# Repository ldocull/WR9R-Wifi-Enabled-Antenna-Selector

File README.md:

# WR9R-Wifi-Enabled-Antenna-Selector
This PCBA provides a method to remotely control antenna selection within a LAN using a standard browser.  I like to operate my HAM station, which is located in the basement, from other areas in or around my home.  This PCB and Firmware upgrade was easy to apply to my existing [Ameritron RCS-8V](https://mfjenterprises.com/products/rcs-8v) Antenna Selector control box while still maintaining manual control when I am in the basement radio-shack. 

## Key features:

- Directly fits within the existing enclosure
- Supports original manual control but adds remote control 
  (Changing the antenna choice at the front panel at any time, resets the device to the manual selection mode)
- Browser buttons can be named through the browser to support antenna upgrades

## Assembly Installation:

 The control wires were clipped from the back terminal strip and landed to the rear of the PCBA as shown above.
- New wires were the placed from the "To Relays" header to the terminal strip
- 12VDC power was picked up at the DC jack on the rear of the enclosure -- but could be picked up after the from panel switch on the front PCBA.

## Setup:

 The software can be modified and hard coded to your network. Otherwise you can set it up using a phone or other internet-ready device. Connect to the Wifi hotspot generated by the Antenna Selector interface that looks like:  *WR9RasNNN*,  where *NNN* is a somewhat random number.
- Password is '*12345678*'
- On the same device, use a browser to then go to the host address:  https://192.168.4.1/SSID

- There, enter the SSID and Password for the network you wish to use within your LAN
- If you're plugged into the wifi module of the new PCBA with a USB cable, you can use a terminal session to see the new IP.  Otherwise. you will need to log into your router to find the new address assigned to the device.

## Antenna Names:
The buttons on the main screen can be renamed at any time. Just go to **htpps://*yourIPadd*/NAMES**

73
-[WR9R](http://wr9r.com/) 

___
Let us know that this work has been helpful to you.  Any proceeds will be used to offset expenses and further the art.

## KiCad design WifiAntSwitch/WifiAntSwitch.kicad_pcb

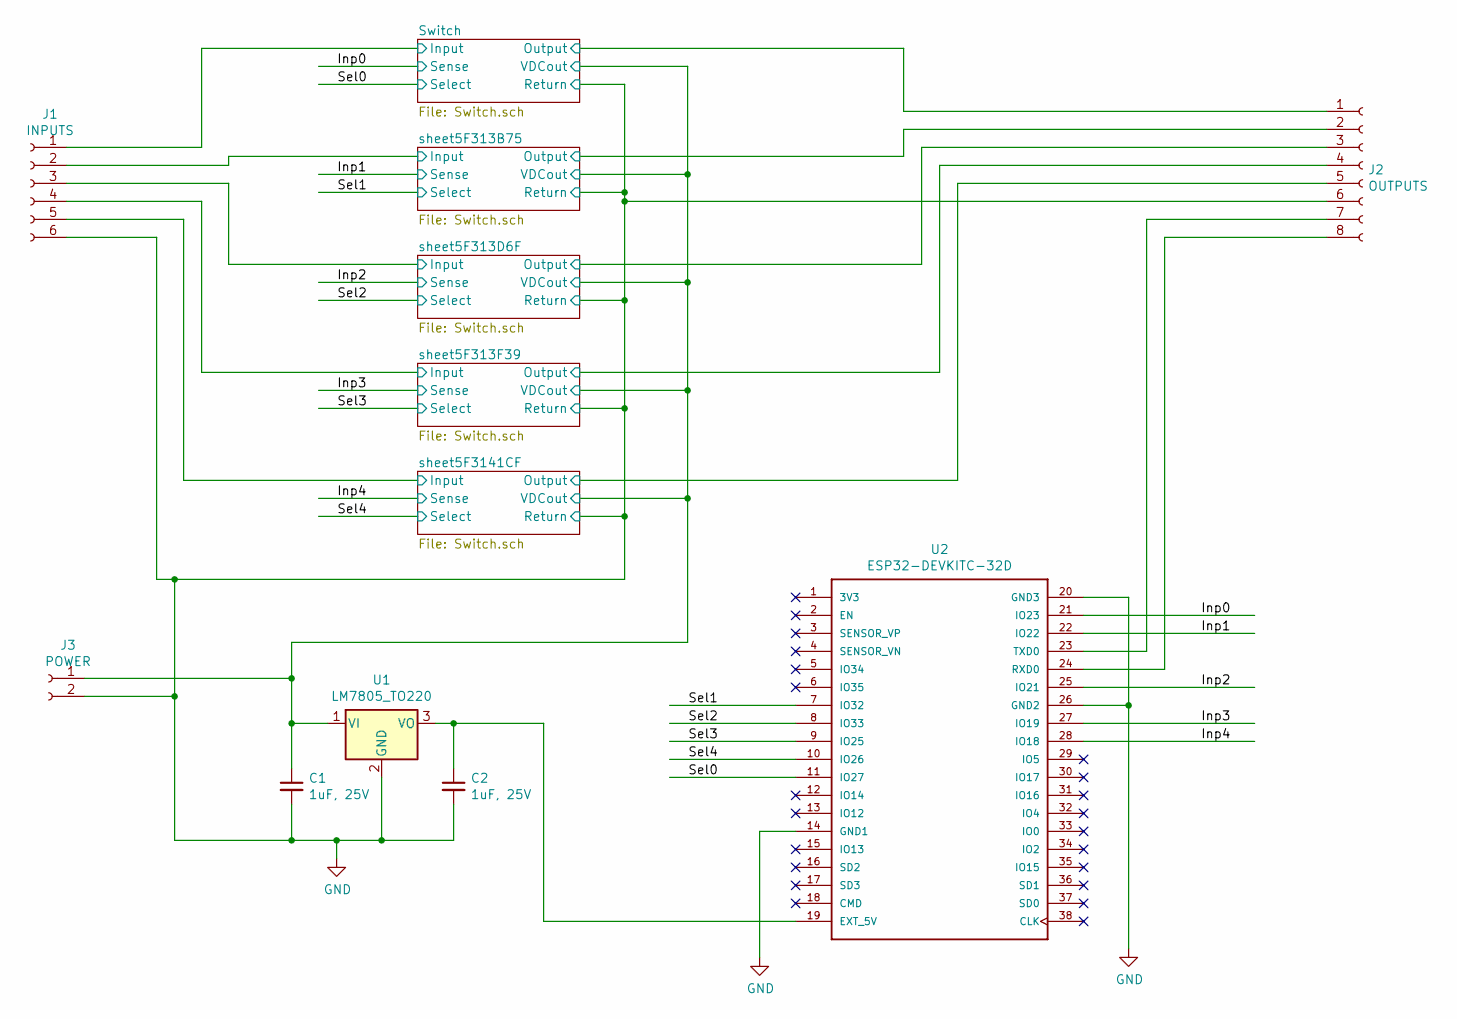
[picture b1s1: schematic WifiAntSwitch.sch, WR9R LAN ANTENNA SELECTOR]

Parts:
C1, C2: 1uF, 25V; C_0805_2012Metric
J1: INPUTS; PinHeader_1x06_P2.54mm_Vertical
J2: OUTPUTS; PinHeader_1x08_P2.54mm_Vertical
J3: POWER; PinHeader_1x02_P2.54mm_Vertical
U1: LM7805_TO220; TO-220-3_Horizontal_TabDown
U2: ESP32-DEVKITC-32D; MODULE_ESP32-DEVKITC-32D

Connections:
/Inp0: U2.21 (IO23); also elsewhere on the board
/Inp1: U2.22 (IO22); also elsewhere on the board
/Inp2: U2.25 (IO21); also elsewhere on the board
/Inp3: U2.27 (IO19); also elsewhere on the board
/Inp4: U2.28 (IO18); also elsewhere on the board
/Sel0: U2.11 (IO27); also elsewhere on the board
/Sel1: U2.7 (IO32); also elsewhere on the board
/Sel2: U2.8 (IO33); also elsewhere on the board
/Sel3: U2.9 (IO25); also elsewhere on the board
/Sel4: U2.10 (IO26); also elsewhere on the board
/Switch/Input: J1.1; also elsewhere on the board
/Switch/Output: J2.1; also elsewhere on the board
/Switch/VDCout: C1.1, J3.1, U1.1 (VI); also elsewhere on the board
/sheet5F313B75/Input: J1.2; also elsewhere on the board
/sheet5F313B75/Output: J2.2; also elsewhere on the board
/sheet5F313D6F/Input: J1.3; also elsewhere on the board
/sheet5F313D6F/Output: J2.3; also elsewhere on the board
/sheet5F313F39/Input: J1.4; also elsewhere on the board
/sheet5F313F39/Output: J2.4; also elsewhere on the board
/sheet5F3141CF/Input: J1.5; also elsewhere on the board
/sheet5F3141CF/Output: J2.5; also elsewhere on the board
GND: C1.2, C2.2, J1.6, J2.6, J3.2, U1.2 (GND), U2.14 (GND1), U2.20 (GND3), U2.26 (GND2); also elsewhere on the board
unnamed: C2.1, U1.3 (VO), U2.19 (EXT_5V)
unnamed: J2.7, U2.23 (TXD0)
unnamed: J2.8, U2.24 (RXD0)

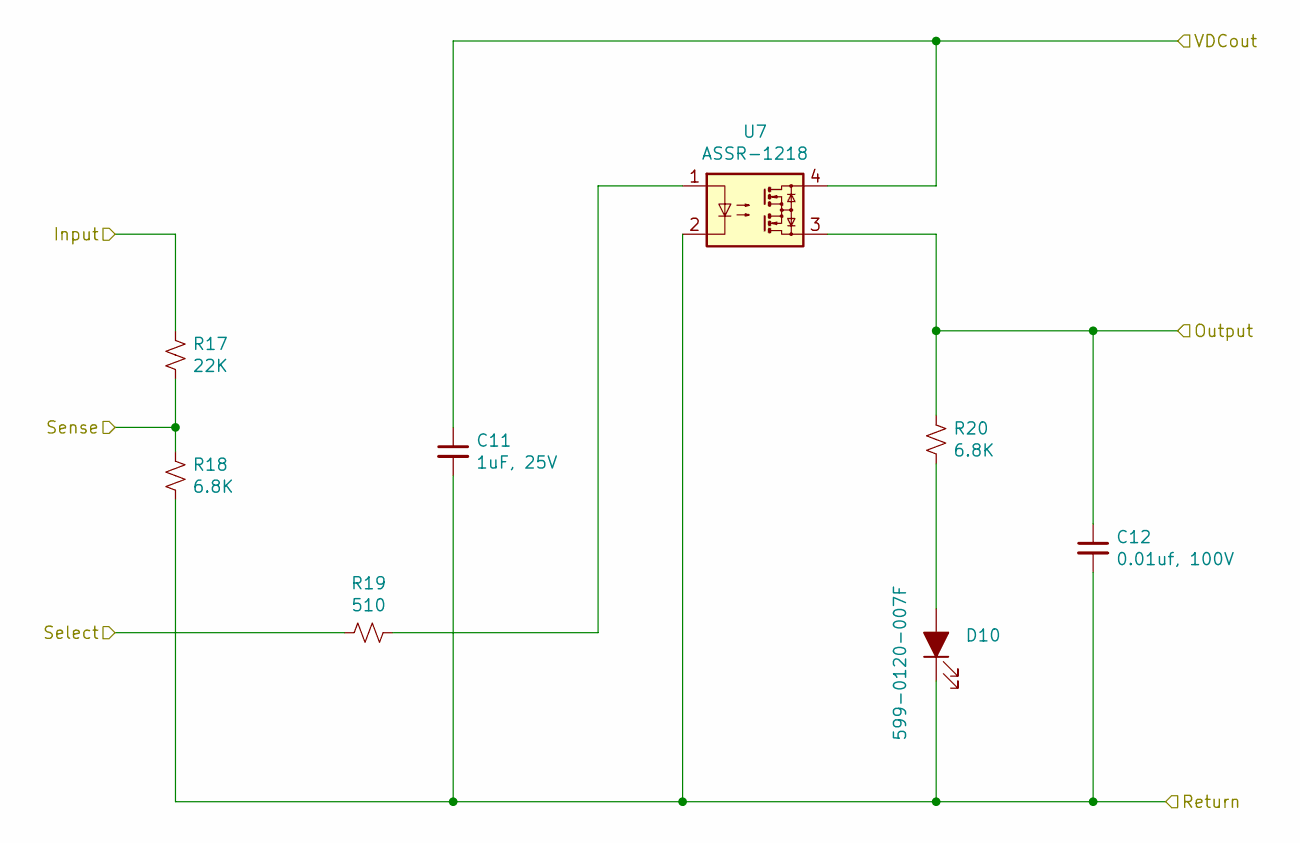
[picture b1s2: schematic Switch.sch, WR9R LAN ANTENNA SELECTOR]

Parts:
C3: 1uF, 25V; C_0805_2012Metric
C4: 0.01uf, 100V; C_0805_2012Metric
D10: 599-0120-007F; LED_0805_2012Metric
R1: 22K; R_0805_2012Metric
R2, R4: 6.8K; R_0805_2012Metric
R3: 510; R_0805_2012Metric
U3: ASSR-1218; SO-4_4.4x4.3mm_P2.54mm

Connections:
/Inp0: R1.1, R2.1; also elsewhere on the board
/Sel0: R3.2; also elsewhere on the board
/Switch/Input: R1.2; also elsewhere on the board
/Switch/Output: C4.1, R4.1, U3.3; also elsewhere on the board
/Switch/VDCout: C3.1, U3.4; also elsewhere on the board
GND: C3.2, C4.2, D10.1 (K), R2.2, U3.2; also elsewhere on the board
unnamed: R3.1, U3.1

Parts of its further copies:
C5, C7, C9, C11: 1uF, 25V; C_0805_2012Metric
C6, C8, C10, C12: 0.01uf, 100V; C_0805_2012Metric
D2, D4, D6, D8: 599-0120-007F; LED_0805_2012Metric
R5, R9, R13, R17: 22K; R_0805_2012Metric
R6, R8, R10, R12, R14, R16, R18, R20: 6.8K; R_0805_2012Metric
R7, R11, R15, R19: 510; R_0805_2012Metric
U4, U5, U6, U7: ASSR-1218; SO-4_4.4x4.3mm_P2.54mm

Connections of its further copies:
/Inp1: R5.1, R6.1; also elsewhere on the board
/Inp2: R9.1, R10.1; also elsewhere on the board
/Inp3: R13.1, R14.1; also elsewhere on the board
/Inp4: R17.1, R18.1; also elsewhere on the board
/Sel1: R7.2; also elsewhere on the board
/Sel2: R11.2; also elsewhere on the board
/Sel3: R15.2; also elsewhere on the board
/Sel4: R19.2; also elsewhere on the board
/Switch/VDCout: C5.1, C7.1, C9.1, C11.1, U4.4, U5.4, U6.4, U7.4; also elsewhere on the board
/sheet5F313B75/Input: R5.2; also elsewhere on the board
/sheet5F313B75/Output: C6.1, R8.1, U4.3; also elsewhere on the board
/sheet5F313D6F/Input: R9.2; also elsewhere on the board
/sheet5F313D6F/Output: C8.1, R12.1, U5.3; also elsewhere on the board
/sheet5F313F39/Input: R13.2; also elsewhere on the board
/sheet5F313F39/Output: C10.1, R16.1, U6.3; also elsewhere on the board
/sheet5F3141CF/Input: R17.2; also elsewhere on the board
/sheet5F3141CF/Output: C12.1, R20.1, U7.3; also elsewhere on the board
GND: C5.2, C6.2, C7.2, C8.2, C9.2, C10.2, C11.2, C12.2, D2.1 (K), D4.1 (K), D6.1 (K), D8.1 (K), R6.2, R10.2, R14.2, R18.2, U4.2, U5.2, U6.2, U7.2; also elsewhere on the board
unnamed: D4.2 (A), R8.2
unnamed: D6.2 (A), R12.2
unnamed: D8.2 (A), R16.2
unnamed: R7.1, U4.1
unnamed: R11.1, U5.1
unnamed: R15.1, U6.1
unnamed: R19.1, U7.1

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
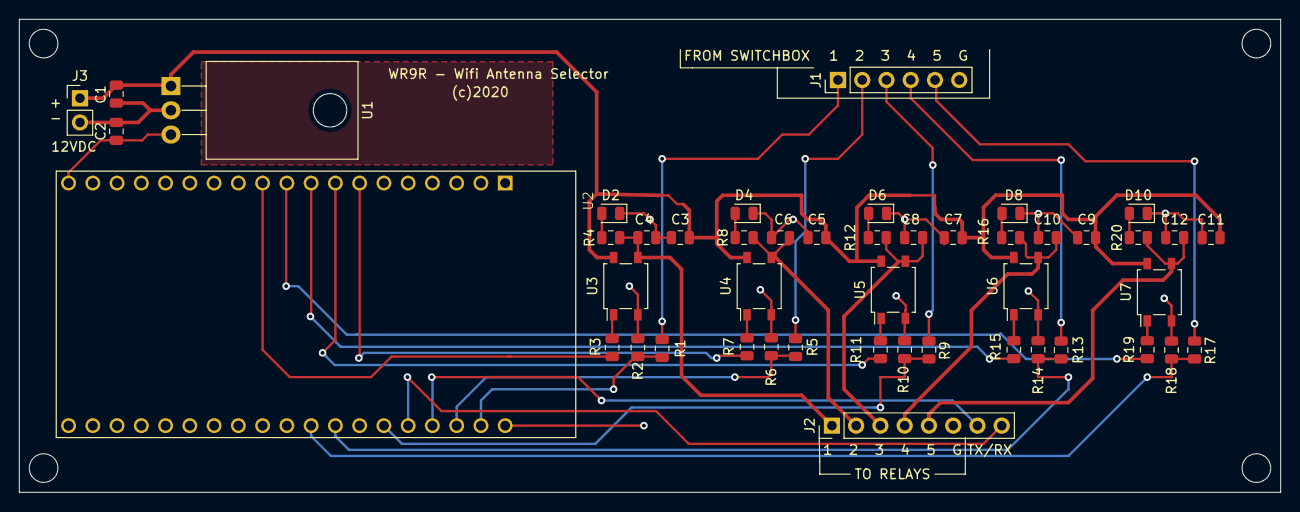
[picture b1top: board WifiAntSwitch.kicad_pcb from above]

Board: 2 copper layers, 132.1 x 49.5 mm, 47 parts (0 on the bottom side), 35 nets.

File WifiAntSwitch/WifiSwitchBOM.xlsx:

Id | Designator | Package | Quantity | Designation | Supplier and ref | Column1 | _1
1 | U2 | MODULE_ESP32-DEVKITC-32D | 1 | ESP32-DEVKITC-32D | 356-ESP32-DEVKITC32D
4 | U1 | TO-220-3_Horizontal_TabDown | 1 | LM7805_TO220 | LM7805CT/NOPB
5 | D9,D7,D5,D3,D1 | D_3220_8050Metric | 5 | RS07D-HM3-08 | RS07D-HM3-08
6 | U7,U6,U5,U4,U3 | SO-4_4.4x4.3mm_P2.54mm | 5 | ASSR-1218 | ASSR-1218-003E
7 | R20,R18,R16,R14,R12,R10,R8,R6,R4,R2 | R_0805_2012Metric | 10 | 6.8K | CR0805-FX-6801ELF
8 | R19,R15,R11,R7,R3 | R_0805_2012Metric | 5 | 510 | CR0805-FX-5100ELF
9 | R17,R13,R9,R5,R1 | R_0805_2012Metric | 5 | 22K | CR0805-FX-2202ELF
12 | D10,D8,D6,D4,D2 | LED_0805_2012Metric | 5 | 599-0120-007F | 599-0120-007F
13 | C12,C10,C8,C6,C4 | C_0805_2012Metric | 5 | 0.01uf, 100V | HMF212B7103KGHT
14 | C11,C9,C7,C5,C3,C2,C1 | C_0805_2012Metric | 7 | 1uF, 25V | 08053G105MAT2A

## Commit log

2020-08-21 Firmware Source
    This is an Arduino-based solution developed in MSCode and PlatformIO
2020-08-21 Hardware Source
    These files contain schematic and PCB artwork developed in KiCAD
2020-08-21 Update README.md
    This PCBA and Firmware provides a method to remotely control antenna selection within a LAN using a standard browser.
2022-12-28 Python Script for Automation
    This Python Script is for shack automation. The script polls my K3 every 2 seconds and looks for band changes. If the band changes, the WR9R Antenna Switch setting is retrieved from the lookup table 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
2022-12-29 WR9R Auto Band Switch Manager
    This will automatically select the antenna based on band selected
    on the K3. Updates allow better control of when tuning of an external
    ATU will be enabled (small signal output) and for how long.
2022-12-31 WR9R Auto Band Switch Manager
    Improved startup for cases such as no logging or other software running.
    This will automatically select the antenna based on band selected
    on the K3. Updates allow better control of when tuning of an external
    ATU will be enabled (small signal output) and for how long.
2022-12-31 WR9R Auto Band Switch Manager
    (A little more code cleanup) ..This will automatically select the antenna based on band selected
    on the K3. Updates allow better control of when tuning of an external
    ATU will be enabled (small signal output) and for how long.
2023-01-01 WR9R Auto Band Switch Manager
    Cleanup and improved robustness. Also added KAT500 support to fully automate the band switch from radio through internal/external tuner to antenna.
2023-01-01 Station Automation Python Script
    This script runs in background monitoring band changes and setting the appropriate Wifi-Enabled-Selector output as well as configuring and tuning the Elecraft KAT500 and/or applying a 'tune' signal t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
2023-01-02 Python 3.11 Version
    Same as 2.7 functionally -- but with optional popup to allow confirmation of tuning (clear frequency courtesy check.)
2023-01-03 Station Automation Script - py3.11
    This script checks the selected band from an Elecraft K3, and automatically adjusts the KAT500 and WR9R-Wifi-Selector accordingly.
2023-01-04 WR9R Station Control - Automatic Switching and Tuning (Python3)
    Script monitors the band switching and sets KAT500 and WR9R-Wifi-Selector according to selected band. Small UI allows for remote operations with VNC or another remote desktop tool.
2024-12-30 Web Switch Monitor
    This Python examples provides a remote control panel
2025-04-21 Upgrade to allow direct monitor of Elecraft K3
    This upgrade allows for the switch to instantly follow the rig.
    The return messages are monitored via RS232 and the switch follows the settings on the FREQS page.
    Frequency bands are defined in whole MHZ, comma separated, and a semicolon at the end of each line.

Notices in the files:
WifiAntSwitch/WifiAntSwitch.kicad_pcb:
(c)2020
